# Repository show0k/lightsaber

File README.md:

#ENSEA-lightsaber

Project made during the ENSEA 2nd year.
More documentation will be here after the new version of the sound board.

Official website [french] lightsaber.ensea.fr

#Credits
Project made by Cédric P. (tiritchi) and Théo S. (show0k) directed by our teacher M. Tauvel.

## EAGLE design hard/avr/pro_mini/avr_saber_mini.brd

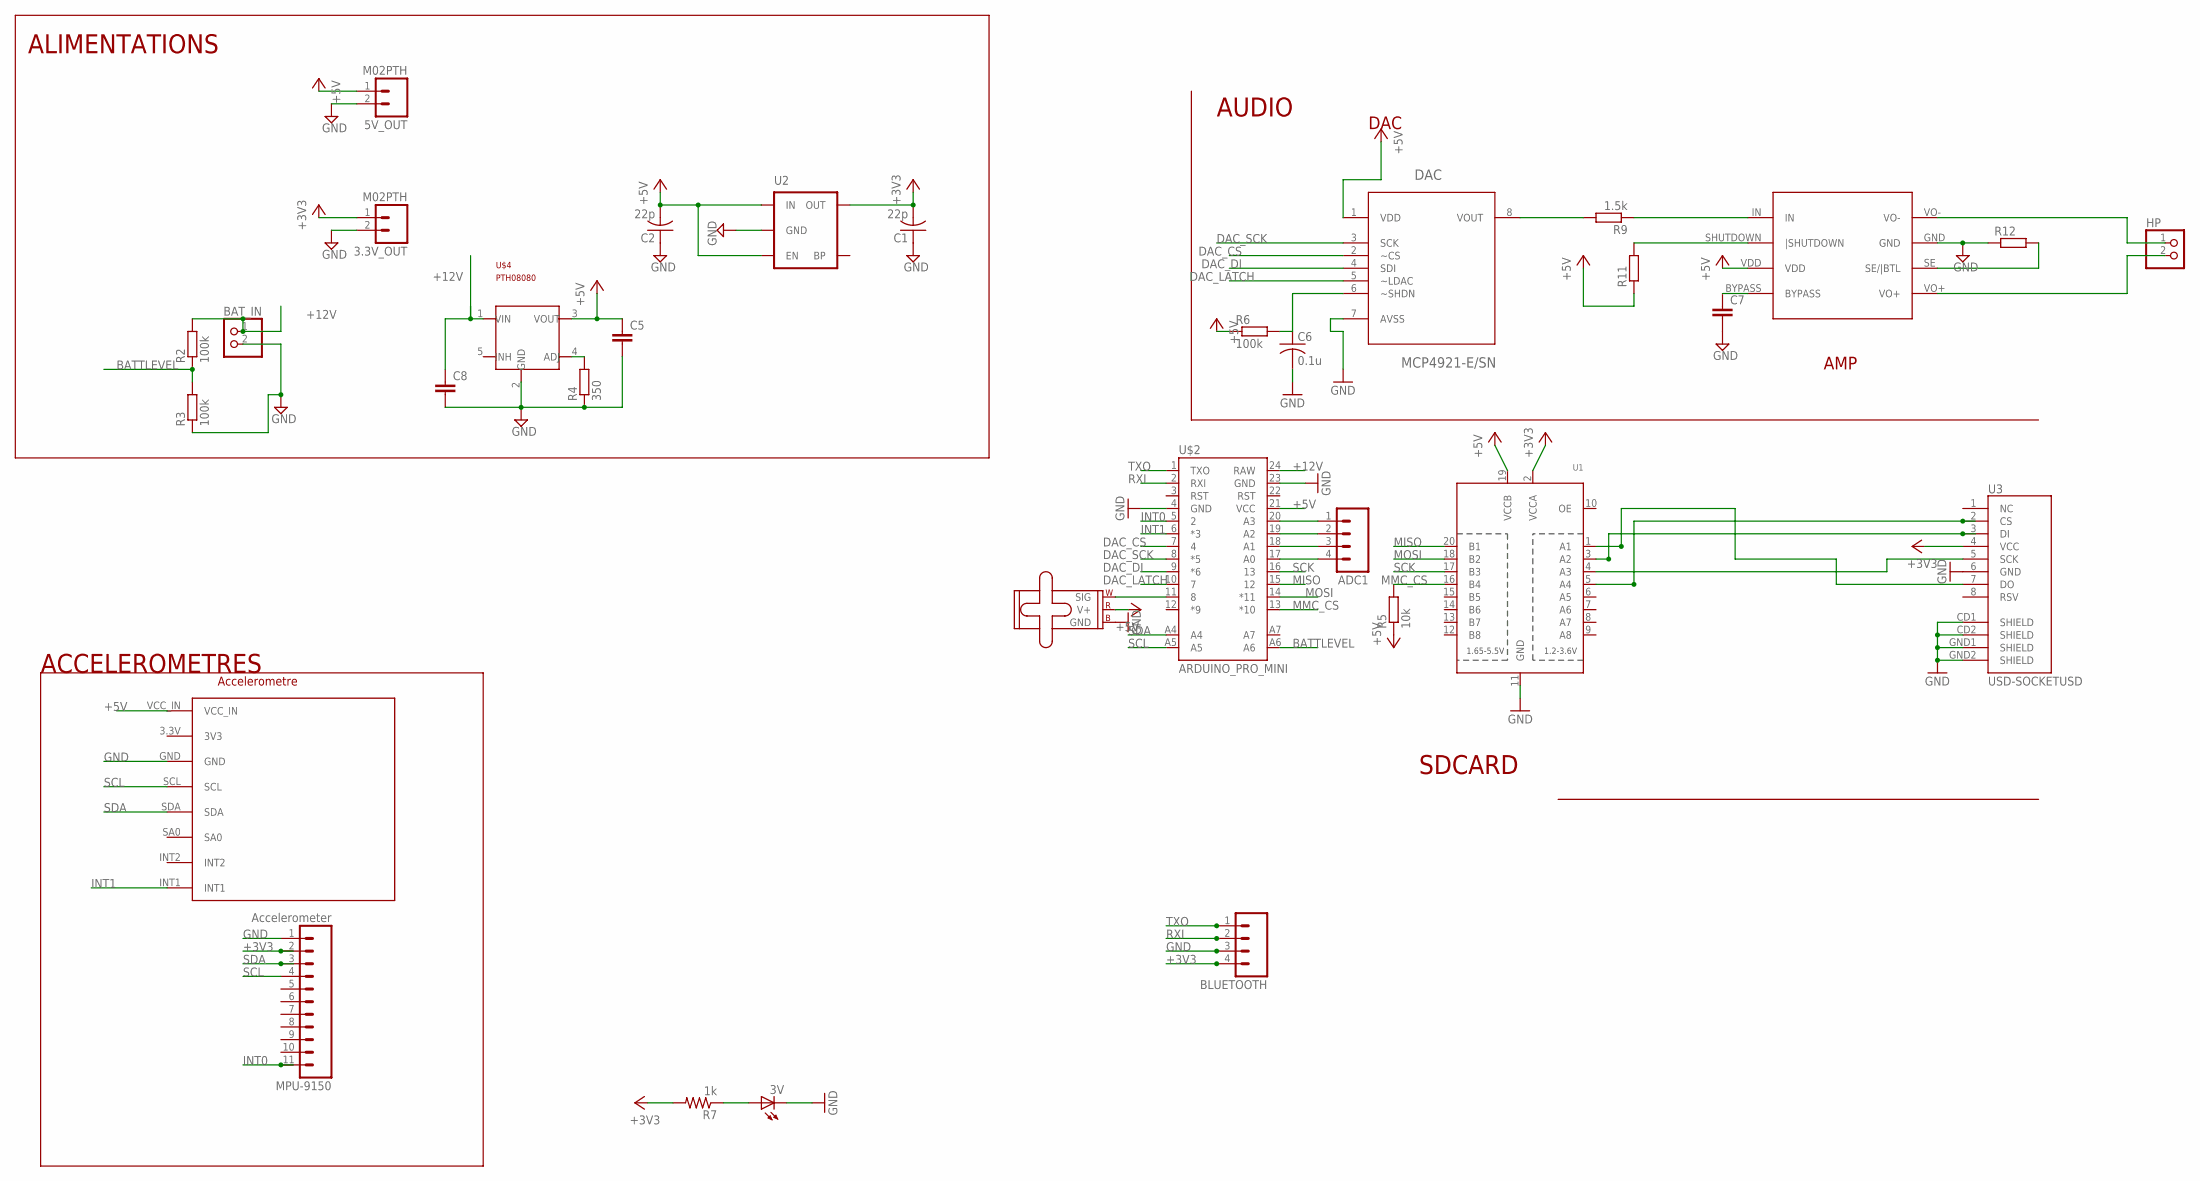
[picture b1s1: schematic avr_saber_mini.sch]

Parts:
3.3V_OUT, 5V_OUT: M02PTH; 1X02
3V: LEDSML0805; SML0805
ADC1: M04PTH; 1X04
BAT_IN: PINHD-1X2; 1X02
BLUETOOTH: M04PTH; 1X04
C1, C2: 22p; C0805
C5, C8: C-EUC1206K; C1206K
C6: 0.1u; C0805
C7: C-EU025-025X050; C025-025X050
DAC: MCP4921-E/SN; SOIC8-N_MC
HP: PINHD-1X2; 1X02
LED1: SMALL_SERVO; 1X03
MMA8451: DEV; MMA8451
MPU-9150: Accelerometer; 1X11
R2, R3, R6: 100k; R0805
R4: 350; R0805
R5: 10k; R0805
R7: 1k; M0805
R9: 1.5k; R0805
R11, R12: R-EU_R0805; R0805
U1: TXB0108PWR; TSSOP20
U2: MIC52053.3V; SOT23-5
U3: USD-SOCKETUSD; USD-SOCKET-PP
U$1: TPA0211
U$2: ARDUINO_PRO_MINI
U$4: PTH08080; PTH08080EUF

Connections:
+3V3: 3.3V_OUT.1, BLUETOOTH.4, C1.2, MPU-9150.2, R7.2, U1.2 (VCCA), U2.5 (OUT), U3.4 (VCC)
+5V: 5V_OUT.1, C2.2, C5.1, DAC.1 (VDD), LED1.2 (V+), MMA8451.VCC_IN, R5.1, R6.1, R11.1, U1.19 (VCCB), U2.1 (IN), U2.3 (EN), U$1.VDD, U$2.21 (VCC), U$4.3 (VOUT)
+12V: BAT_IN.1, C8.1, R2.2, U$2.24 (RAW), U$4.1 (VIN)
BATTLEVEL: R2.1, R3.2, U$2.A6
DAC_CS: DAC.2 (~CS), U$2.7 (4)
DAC_DI: DAC.4 (SDI), U$2.9 (*6)
DAC_LATCH: DAC.5 (~LDAC), U$2.10 (7)
DAC_SCK: DAC.3 (SCK), U$2.8 (*5)
GND: 3.3V_OUT.2, 3V.C, 5V_OUT.2, BAT_IN.2, BLUETOOTH.3, C1.1, C2.1, C5.2, C6.2, C7.2, C8.2, DAC.7 (AVSS), LED1.3 (GND), MMA8451.GND, MPU-9150.1, R3.1, R4.1, R12.1, U1.11 (GND), U2.2 (GND), U3.6 (GND), U3.CD1 (SHIELD), U3.CD2 (SHIELD), U3.GND1 (SHIELD), U3.GND2 (SHIELD), U$1.GND, U$2.4 (GND), U$2.23 (GND), U$4.2 (GND)
INT0: MPU-9150.11, U$2.5 (2)
INT1: MMA8451.INT1, U$2.6 (*3)
MISO: U1.20 (B1), U$2.15 (12)
MMC_CS: R5.2, U1.16 (B4), U$2.13 (*10)
MOSI: U1.18 (B2), U$2.14 (*11)
unnamed: R9.1, U$1.IN
unnamed: ADC1.1, U$2.20 (A3)
unnamed: R4.2, U$4.4 (ADJ)
unnamed: U1.4 (A3), U3.5 (SCK)
unnamed: U1.1 (A1), U3.7 (DO)
unnamed: U1.5 (A4), U3.2 (CS)
unnamed: 3V.A, R7.1
unnamed: U1.3 (A2), U3.3 (DI)
unnamed: ADC1.2, U$2.19 (A2)
unnamed: DAC.8 (VOUT), R9.2
unnamed: ADC1.3, U$2.18 (A1)
unnamed: ADC1.4, U$2.17 (A0)
unnamed: LED1.1 (SIG), U$2.11 (8)
unnamed: C6.1, DAC.6 (~SHDN), R6.2
unnamed: HP.1, U$1.VO-
unnamed: C7.1, U$1.BYPASS
unnamed: R11.2, U$1.SHUTDOWN (|SHUTDOWN)
unnamed: R12.2, U$1.SE (SE/|BTL)
RXI: BLUETOOTH.2, U$2.2 (RXI)
SCK: U1.17 (B3), U$2.16 (13)
SCL: MMA8451.SCL, MPU-9150.4, U$2.A5
SDA: MMA8451.SDA, MPU-9150.3, U$2.A4
TXO: BLUETOOTH.1, U$2.1 (TXO)
VO+: HP.2, U$1.VO+

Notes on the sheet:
DAC
AMP
Accelerometre
ALIMENTATIONS
ACCELEROMETRES
AUDIO
SDCARD

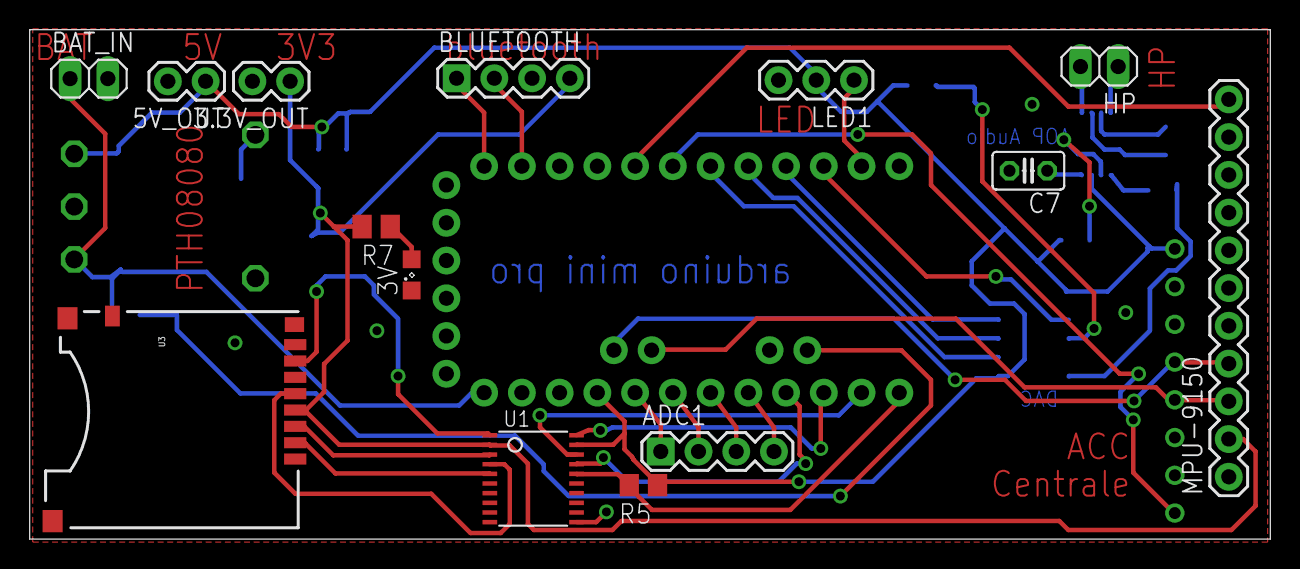
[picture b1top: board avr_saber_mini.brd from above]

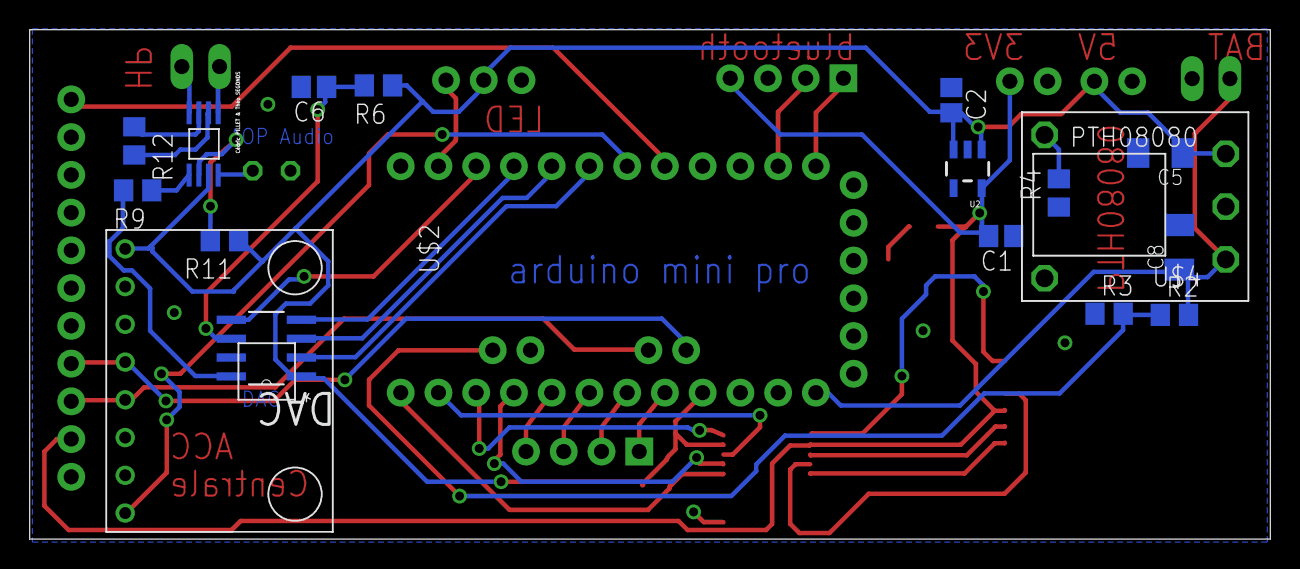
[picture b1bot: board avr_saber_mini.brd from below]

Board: 2 copper layers, 83.5 x 34.3 mm, 32 parts (18 on the bottom side), 38 nets.

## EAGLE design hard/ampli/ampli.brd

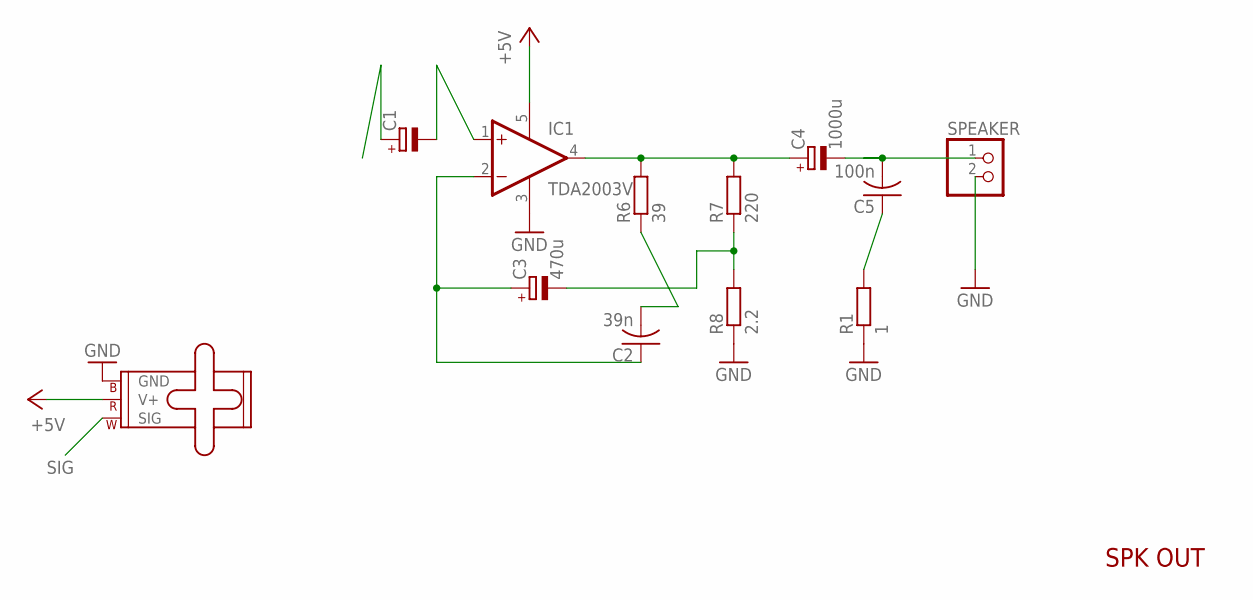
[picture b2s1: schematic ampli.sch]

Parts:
C1: CPOL-EUE2.5-6; E2,5-6
C2: 39n; C0805
C3: 470u; E2,5-6
C4: 1000u; E2,5-6
C5: 100n; C0805
IC1: TDA2003V; CB360
LED: SMALL_SERVO; 1X03
R1: 1; R0805
R6: 39; R0805
R7: 220; R0805
R8: 2.2; R0805
SPEAKER: PINHD-1X2; 1X02

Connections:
+5V: IC1.5 (V+), LED.2 (V+)
GND: IC1.3 (GND), LED.3 (GND), R1.1, R8.1, SPEAKER.2
unnamed: C1.-, IC1.1 (+IN)
unnamed: C2.2, R6.1
unnamed: C5.1, R1.2
unnamed: C3.-, R7.1, R8.2
unnamed: C2.1, C3.+, IC1.2 (-IN)
unnamed: C4.-, C5.2, SPEAKER.1
unnamed: C4.+, IC1.4 (OUT), R6.2, R7.2
SIG: C1.+, LED.1 (SIG)

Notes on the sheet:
SPK OUT

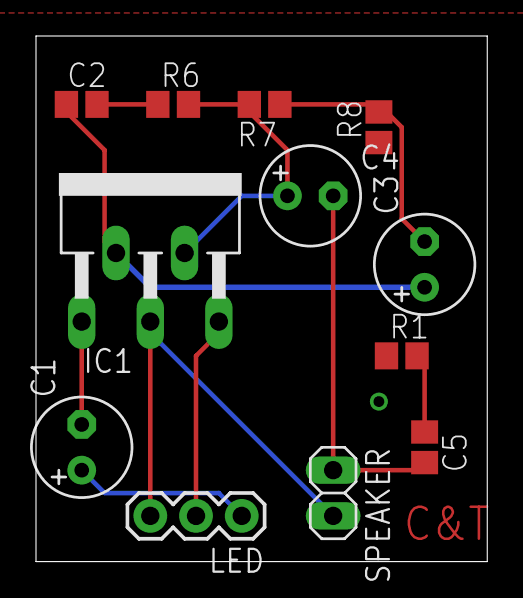
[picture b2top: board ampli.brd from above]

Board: 2 copper layers, 25.1 x 29.2 mm, 12 parts (0 on the bottom side), 10 nets.

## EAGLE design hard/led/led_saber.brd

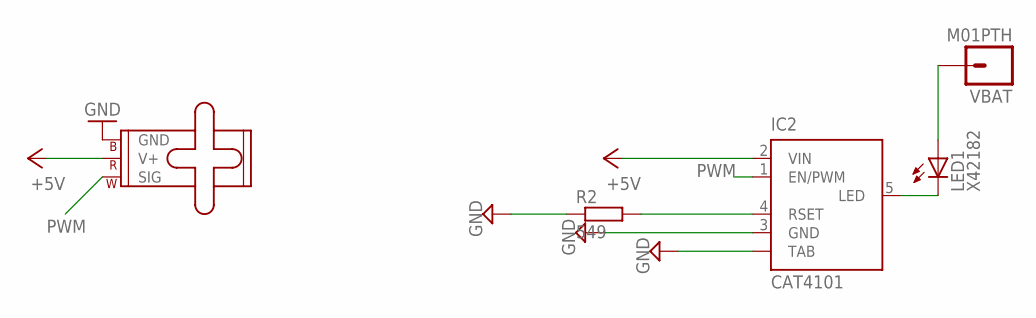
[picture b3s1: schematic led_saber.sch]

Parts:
IC2: CAT4101; TO263_5
LED: SMALL_SERVO; 1X03
LED1: X42182; Z-POWER-LED-DOME-TYPE
R2: 549; R0805
VBAT: M01PTH; 1X01

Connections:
+5V: IC2.2 (VIN), LED.2 (V+)
GND: IC2.3 (GND), IC2.TAB, LED.3 (GND), R2.1
unnamed: IC2.5 (LED), LED1.C
unnamed: IC2.4 (RSET), R2.2
unnamed: LED1.A, VBAT.1
PWM: IC2.1 (EN/PWM), LED.1 (SIG)

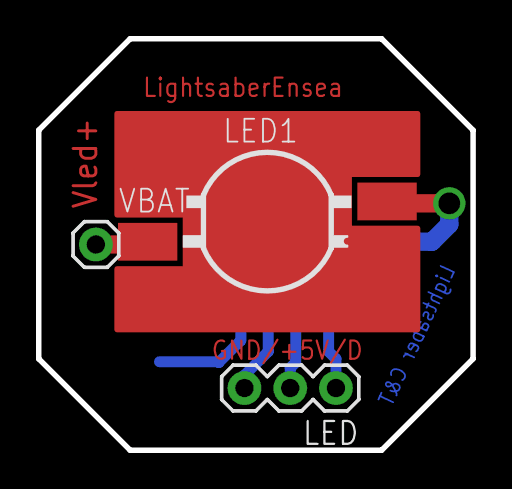
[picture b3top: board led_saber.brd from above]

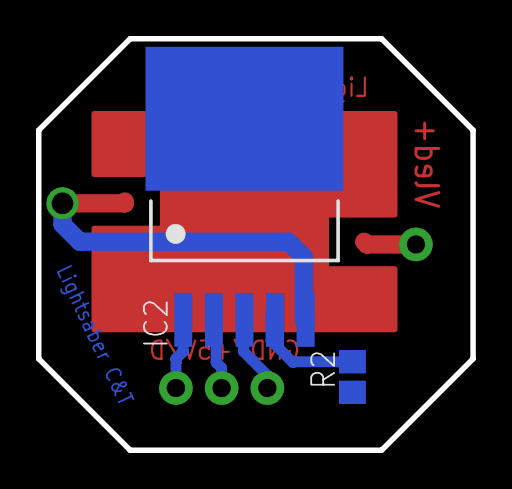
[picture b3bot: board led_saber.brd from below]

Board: 2 copper layers, 24.1 x 22.9 mm, 5 parts (2 on the bottom side), 6 nets.

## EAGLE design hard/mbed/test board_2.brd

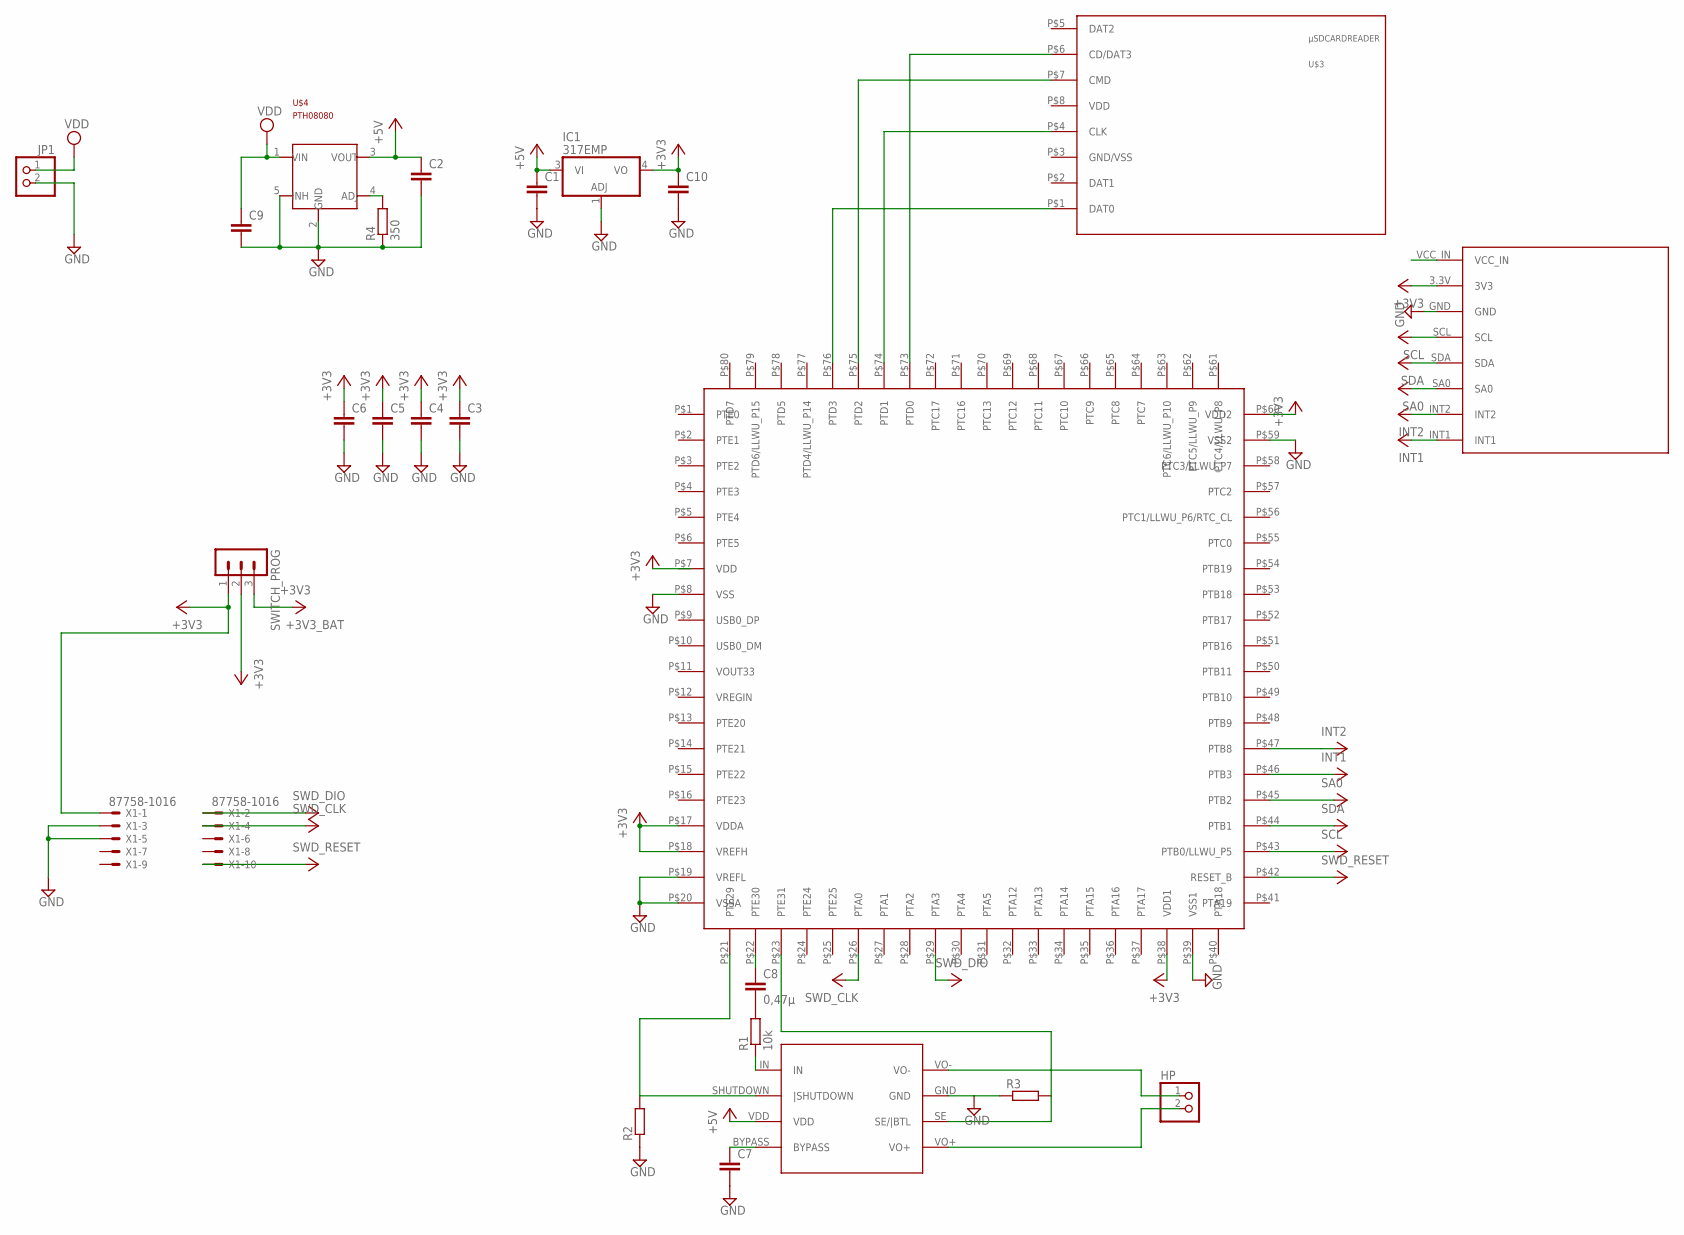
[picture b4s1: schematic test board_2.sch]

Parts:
C1, C2, C3, C4, C5, C6, C9, C10: C-EUC1206K; C1206K
C7: C-EU025-025X050; C025-025X050
C8: 0,47µ; C1206K
HP: PINHD-1X2; 1X02
IC1: 317EMP; SOT223
JP1: PINHD-1X2; 1X02
R1: 10k; R0805
R2, R3: R-EU_R0805; R0805
R4: 350; R0805
SWITCH_PROG: MA03-1
U$1: TPA0211
U$2: KL25Z_LQFP80
U$3: µSDCARDREADER; MICROSD
U$4: PTH08080; PTH08080EUF
U$5: DEV; MMA8451
X1: 87758-1016

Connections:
+3V3: C3.1, C4.1, C5.1, C6.1, SWITCH_PROG.2, U$2.P$17 (VDDA), U$2.P$18 (VREFH), U$2.P$38 (VDD1), U$2.P$60 (VDD2), U$5.3.3V (3V3)
+3V3_BAT: C10.1, IC1.4 (VO), SWITCH_PROG.3
+3V3_SWD: SWITCH_PROG.1, X1.1
+5V: C1.1, C2.1, IC1.3 (VI), U$1.VDD, U$4.3 (VOUT)
GND: C1.2, C2.2, C3.2, C4.2, C5.2, C6.2, C7.2, C9.2, C10.2, IC1.1 (ADJ), JP1.2, R2.1, R3.1, R4.1, U$1.GND, U$2.P$8 (VSS), U$2.P$19 (VREFL), U$2.P$20 (VSSA), U$2.P$39 (VSS1), U$2.P$59 (VSS2), U$4.2 (GND), U$4.5 (INH), U$5.GND, X1.3, X1.5
INT1: U$2.P$46 (PTB3), U$5.INT1
INT2: U$2.P$47 (PTB8), U$5.INT2
unnamed: U$2.P$76 (PTD3), U$3.P$1 (DAT0)
unnamed: U$2.P$73 (PTD0), U$3.P$6 (CD/DAT3)
unnamed: U$2.P$75 (PTD2), U$3.P$7 (CMD)
unnamed: U$2.P$74 (PTD1), U$3.P$4 (CLK)
unnamed: C8.2, R1.2
unnamed: C7.1, U$1.BYPASS
unnamed: HP.1, U$1.VO-
unnamed: R1.1, U$1.IN
unnamed: C8.1, U$2.P$22 (PTE30)
unnamed: R2.2, U$1.SHUTDOWN (|SHUTDOWN), U$2.P$21 (PTE29)
unnamed: R3.2, U$1.SE (SE/|BTL), U$2.P$23 (PTE31)
unnamed: R4.2, U$4.4 (ADJ)
SA0: U$2.P$45 (PTB2), U$5.SA0
SCL: U$2.P$43 (PTB0/LLWU_P5), U$5.SCL
SDA: U$2.P$44 (PTB1), U$5.SDA
SWD_CLK: U$2.P$26 (PTA0), X1.4
SWD_DIO: U$2.P$29 (PTA3), X1.2
SWD_RESET: U$2.P$42 (RESET_B), X1.10
VDD: C9.1, JP1.1, U$4.1 (VIN)
VO+: HP.2, U$1.VO+

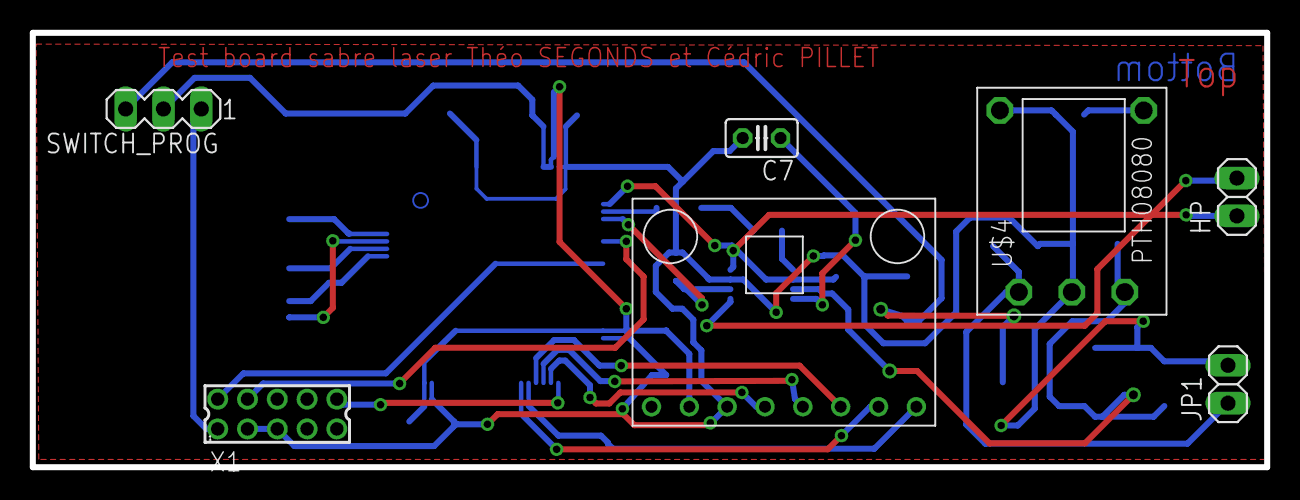
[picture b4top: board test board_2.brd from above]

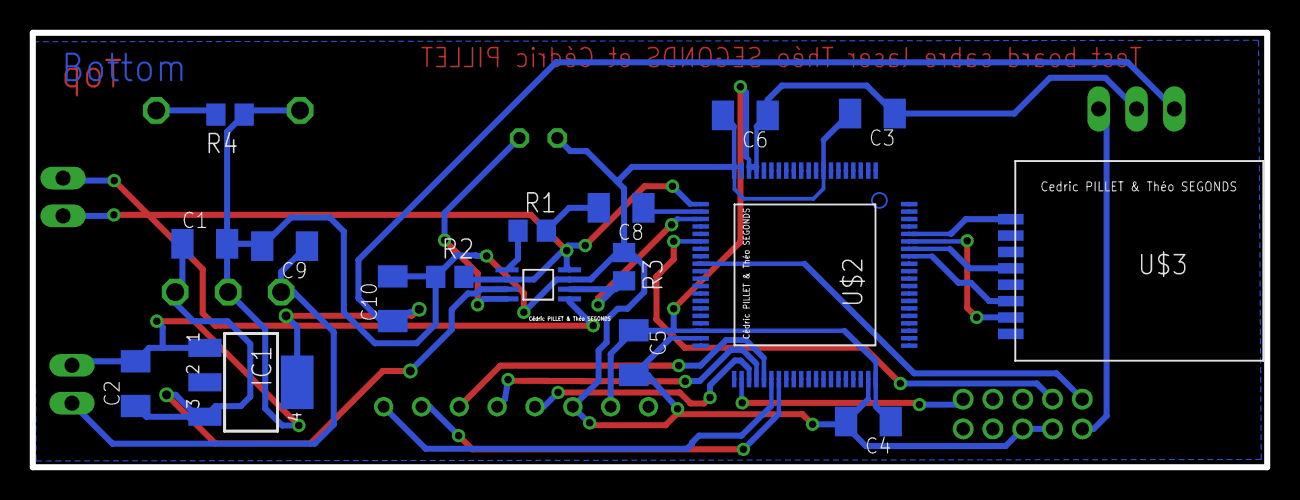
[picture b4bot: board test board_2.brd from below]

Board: 2 copper layers, 82.9 x 29.2 mm, 24 parts (17 on the bottom side), 27 nets.

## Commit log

2014-06-02 akout cartes
2014-06-02 Ajout microSD
2014-06-02 ajout leds
2014-06-03 trying to route
2014-06-03 ajout led (non finie) + shematic avec pro mini
2014-06-03 Carte led puissance terminée
2014-06-03 Ajout noms sur la carte
2014-06-03 new card with mini pro
2014-06-05 ajout divers
2014-06-05 correction inhibit pth
2014-06-06 Ajout 9150
2014-06-06 c'était moche
2014-06-06 new version
2014-06-06 board v2
2014-06-08 ajout divers soft
2014-06-08 gggg
2014-06-10 ajout ampli audio + code
2014-06-12 ajout site
2014-06-12 ajout modif page web
2014-06-13 changement arboresence
2014-06-13 changement arbo
2014-06-14 ajout readme divers
2014-06-14 add some readme
2014-06-15 modif website
2014-06-29 ajout de la dernière version de carte

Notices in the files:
parts and their libraries:
SparkFun-Electromechanical: Licensing: CC v3.0 Share-Alike You are welcome to use this library for commercial purposes.
